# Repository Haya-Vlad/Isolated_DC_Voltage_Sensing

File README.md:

# Isolated DC Voltage Sensing

A fully isolated DC bus voltage sensing circuit designed for power electronics applications, capable of sensing **0–300 V DC** and scaling the signal to a **0–3.3 V ADC range** using the AMC1200 isolation amplifier.

## Table of Contents

- [Overview](#overview)
- [Features](#features)
- [Circuit Architecture](#circuit-architecture)
- [Signal Chain](#signal-chain)
- [Components](#components)
- [Repository Structure](#repository-structure)
- [Hardware Design](#hardware-design)
- [Power Supply](#power-supply)
- [Getting Started](#getting-started)
- [Bill of Materials](#bill-of-materials)
- [License](#license)

---

## Overview

This project implements a  isolated DC voltage sensing solution for high-voltage DC bus measurements (up to 300 V). The circuit uses the **AMC1200** precision isolation amplifier to safely measure high-voltage DC signals while maintaining full electrical isolation between the high-voltage side and the low-voltage (microcontroller/ADC) side.

The design is suitable for use in:
- Motor drives and inverters
- Battery management systems (BMS)
- Solar/PV converters
- DC-DC converters
- Any power electronics system requiring isolated voltage feedback

---

## Features

-  **Input range:** 0–300 V DC
-  **Output range:** 0–3.3 V (direct ADC-compatible)
-  **Full galvanic isolation** via AMC1200
-  **Anti-aliasing filter** at ADC input (150 Ω + 1 nF)
-  **RC pre-filter** for noise reduction before AMC1200
-  **Dual isolated power supply** using LD1117 and L7805 regulators
-  **Unipolar signal path** — no DC offset reference required
-  **MCP6002 op-amp** for output signal conditioning
-  **Designed in Eagle CAD**, Gerber files included
-  **Practically implemented and tested**

---

## Circuit Architecture

```
DC Bus (0–300V)
      │
      ▼
┌─────────────────────┐
│  Resistor Divider   │  620kΩ × 3 on each rail
│  (High-side input   │  which scales to ±250mV differential
│   attenuation)      │
└────────┬────────────┘
         │ Differential ±250mV
         ▼
┌─────────────────────┐
│      AMC1200        │  Isolation amplifier
│  (Isolation Stage)  │  Gain = 8 (±250mV in → ±2V out)
│                     │  Galvanic isolation barrier
└────────┬────────────┘
         │
         ▼
┌─────────────────────┐
│   RC Filter Stage   │  Initial noise suppression
│  (12Ω + 330pF)      │
└────────┬────────────┘
         │
         ▼
┌─────────────────────┐
│      MCP6002        │  Signal conditioning op-amp
│  (Output Scaling)   │  Scales to 0–3.3V ADC range
│                     │  10kΩ feedback network
└────────┬────────────┘
         │
         ▼
┌─────────────────────┐
│  Anti-Aliasing      │  150Ω + 1nF
│  Filter             │  High-frequency noise rejection
└────────┬────────────┘
         │
         ▼
    OUTPUT_TO_ADC (0–3.3V)
```

---

## Signal Chain

1. **Input Attenuation:** The DC bus voltage (0–300 V) is divided by a high-value resistor network  to produce a small differential voltage within the AMC1200's ±250 mV input range.

2. **Isolation (AMC1200):** The AMC1200 isolation amplifier provides galvanic isolation with a fixed gain of 8. The ±250 mV differential input is amplified and transferred across the isolation barrier.

3. **RC Pre-filter:** A 12 Ω + 330 pF RC filter stage provides initial high-frequency noise attenuation immediately after the AMC1200 output.

4. **Signal Conditioning (MCP6002):** The MCP6002 op-amp is configured as a scaling amplifier with a 10 kΩ feedback network. Since the DC bus signal is inherently unipolar, no DC offset reference is required so the signal maps directly into the 0–3.3 V ADC range.

5. **Anti-Aliasing Filter:** A 150 Ω + 1 nF RC filter at the ADC input provides additional high-frequency noise suppression and prevents aliasing during ADC sampling.

---

## Components

| Reference | Component | Value/Part | Description |
|-----------|-----------|------------|-------------|
| U32 | AMC1200 | AMC1200 | Precision isolation amplifier |
| U37 | MCP6002 | MCP6002 | Dual rail-to-rail op-amp |
| CR2 | LD1117 | LD1117 | LDO voltage regulator (isolated side) |
| CR5 | L7805 | L7805 | 5V linear regulator |
| D3, D4 | HSMG-C170 | HSMG-C170 | Green & Red status LED |
| R177–R179, R183–R187 | Resistor | 620 kΩ | Input voltage divider |
| R170, R172–R173 | Resistor | 12 Ω | RC filter resistors |
| R174–R175 | Resistor | 10 kΩ | Op-amp feedback network |
| R259 | Resistor | 150 Ω | Anti-aliasing filter |
| R257, R258 | Resistor | 510 Ω | LED current limiting |
| C122, C125 | Capacitor | 330 pF | RC filter capacitors |
| C126, C127 | Capacitor | 0.1 µF | Decoupling capacitors |
| C153, C155 | Capacitor | 470 µF | Bulk filtering |
| C157, C161–C162 | Capacitor | 100 nF | Supply decoupling |
| C158 | Capacitor | 1 nF | Anti-aliasing filter capacitor |
| L3 | Ferrite Beads | 32mohms | Power supply filter |

---

## Repository Structure

```
isolated-dc-voltage-sensing/
│
├── README.md                  ← You are here
├── LICENSE
├── CHANGELOG.md
│
├── hardware/
│   ├── eagle/
│   │   ├── schematic/         ← .sch Eagle schematic files
│   │   ├── board/             ← .brd Eagle board layout files
│   │   └── libraries/         ← Custom Eagle component libraries (.lbr)
│   ├── gerber/                ← Fabrication-ready Gerber files
│   │   ├── *.GTL              (Top copper)
│   │   ├── *.GBL              (Bottom copper)
│   │   ├── *.GTS              (Top soldermask)
│   │   ├── *.GBS              (Bottom soldermask)
│   │   ├── *.GTO              (Top silkscreen)
│   │   ├── *.DRL              (Drill file)
│   │   └── gerber_readme.md
│   │
│── docs/
    ├── design_notes.md        ← Design decisions and calculations
    ├── signal_chain.md        ← Detailed signal chain analysis
    └── datasheets/            ← Key component datasheets (PDFs)
        ├── AMC1200.pdf
        ├── MCP6002.pdf
        ├── LD1117.pdf
        └── L7805.pdf
```

---

## Hardware Design

The design was created in **Autodesk Eagle CAD**. All source files are located under `hardware/eagle/`.

- **Schematic:** `hardware/eagle/schematic/`
- **Board layout:** `hardware/eagle/board/`
- **Gerber files** (ready for PCB fabrication): `hardware/gerber/`

### Power Supply Architecture

The circuit uses a **dual isolated power supply**:
- **VCC_A / GND_A** — High-voltage (DC bus) side supply, regulated via LD1117
- **VCC_B / GND_B** — Low-voltage (MCU/ADC) side supply, regulated via L7805
- **VCC_12V_A+ / VCC_12V_B+** — 12V rails feeding each regulator

The dual-supply architecture ensures that the isolation barrier of the AMC1200 is maintained across both the signal path and the power supply.

---

## Getting Started

### PCB Fabrication
1. Download the Gerber files from `hardware/gerber/`
2. Upload to your preferred PCB manufacturer (JLCPCB, PCBWay, OSHPark, etc.)
3. Recommended specs: 2-layer, 1.6 mm FR4, HASL or ENIG finish

### Assembly
1. Refer to `hardware/bom/bom.csv` for component sourcing
2. Follow the schematic in `hardware/eagle/schematic/`
3. Pay attention to orientation of AMC1200 and polarized capacitors

### Testing
1. Apply a known DC voltage of 12V to DC_A / DC_B inputs
2. Measure OUTPUT_TO_ADC with a multimeter or oscilloscope
3. Verify scaling linearity against expected values 

---

## Bill of Materials

See [`hardware/BOM`](hardware/BOM/BOM.pdf) for the complete BOM.

---

## License

This project is released under the [MIT License](LICENSE).

---

## Author

**Aditya Gohil**  
Power Electronics Design  
*Designed and practically implemented — May 2026*

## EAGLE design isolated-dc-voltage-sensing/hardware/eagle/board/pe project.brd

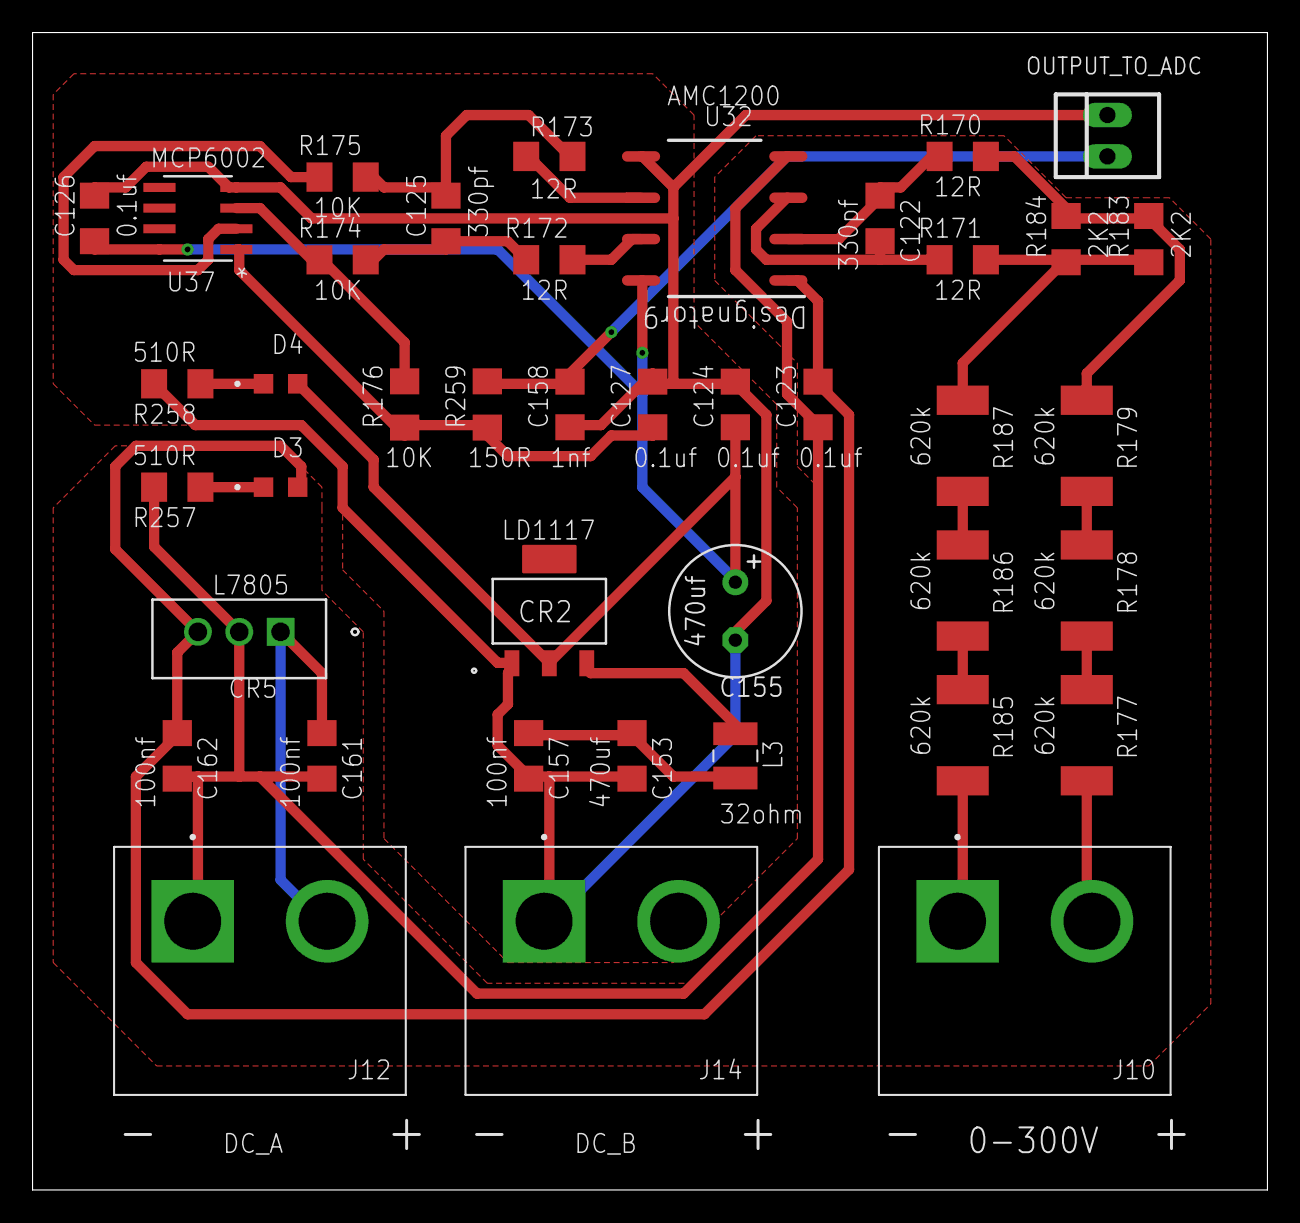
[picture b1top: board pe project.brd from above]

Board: 2 copper layers, 75.9 x 71.1 mm, 41 parts (0 on the bottom side), 27 nets.

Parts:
C122, C125: 330pf; C1206
C123, C124, C126, C127: 0.1uf; C1206
C153: 470uf; C1206
C155: 470uf; E3,5-8
C157, C161, C162: 100nf; C1206
C158: 1nf; C1206
CR2: LD1117; SOT-223_STM
CR5: L7805; TO-220_STM
D3, D4: HSMG-C170; LED_HSMS-C170
J10: 0-300V; TE_5-1437648-7
J12: DC_A; TE_5-1437648-7
J14: DC_B; TE_5-1437648-7
L3: 32ohm; BEADC3225X220N
R170, R171, R172, R173: 12R; R1206
R174, R175, R176: 10K; R1206
R177, R178, R179, R185, R186, R187: 620k; R2512
R183, R184: 2K2; R1206
R257, R258: 510R; R1206
R259: 150R; R1206
U32: AMC1200; DUB0008A_N
U37: MCP6002; SOIC8-N_MC_MCH
X1: OUTPUT_TO_ADC; 22-23-2021

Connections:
AC_V_B_OUT: C127.1, R176.2, R259.1, U37.1
GND_A: C123.1, C161.2, C162.2, CR5.2, J12.1, R257.2, U32.4
GND_B: C124.2, C126.2, C127.2, C153.2, C155.-, C157.2, C158.2, CR2.1, J14.1, R258.2, U32.5, U37.4, X1.2
unnamed: R170.1, R179.1, R183.2, R184.2
unnamed: R171.1, R183.1, R184.1, R187.1
unnamed: C122.1, R170.2, U32.2
unnamed: R172.1, U32.7
unnamed: R173.1, U32.6
unnamed: C125.2, R173.2, R175.1
unnamed: C125.1, R172.2, R174.1
unnamed: R174.2, R176.1, U37.3
unnamed: R177.1, R178.2
unnamed: R178.1, R179.2
unnamed: R175.2, U37.2
unnamed: R185.1, R186.2
unnamed: R186.1, R187.2
unnamed: J10.2, R177.2
unnamed: J10.1, R185.2
unnamed: C122.2, R171.2, U32.3
unnamed: CR2.3, L3.2
unnamed: D3.C, R257.1
unnamed: D4.C, R258.1
OUTPUT_TO_ADC: C158.1, R259.2, X1.1
VCC_12V_A+: C161.1, CR5.1, J12.2
VCC_12V_B: C153.1, C157.1, L3.1
VCC_A: C123.2, C162.1, CR5.3, D3.A, U32.1
VCC_B: C124.1, C126.1, C155.+, CR2.2, D4.A, U32.8, U37.8

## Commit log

2026-05-04 Uploading all the necessary changes
2026-05-04 Uploaded all the necessary docs
2026-05-04 Update README.md for clarity and corrections
2026-05-04 Fix link to Bill of Materials PDF

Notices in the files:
parts and their libraries:
COPYRIGHT: Copyright (C) 2026 Ultra Librarian. All rights reserved.
